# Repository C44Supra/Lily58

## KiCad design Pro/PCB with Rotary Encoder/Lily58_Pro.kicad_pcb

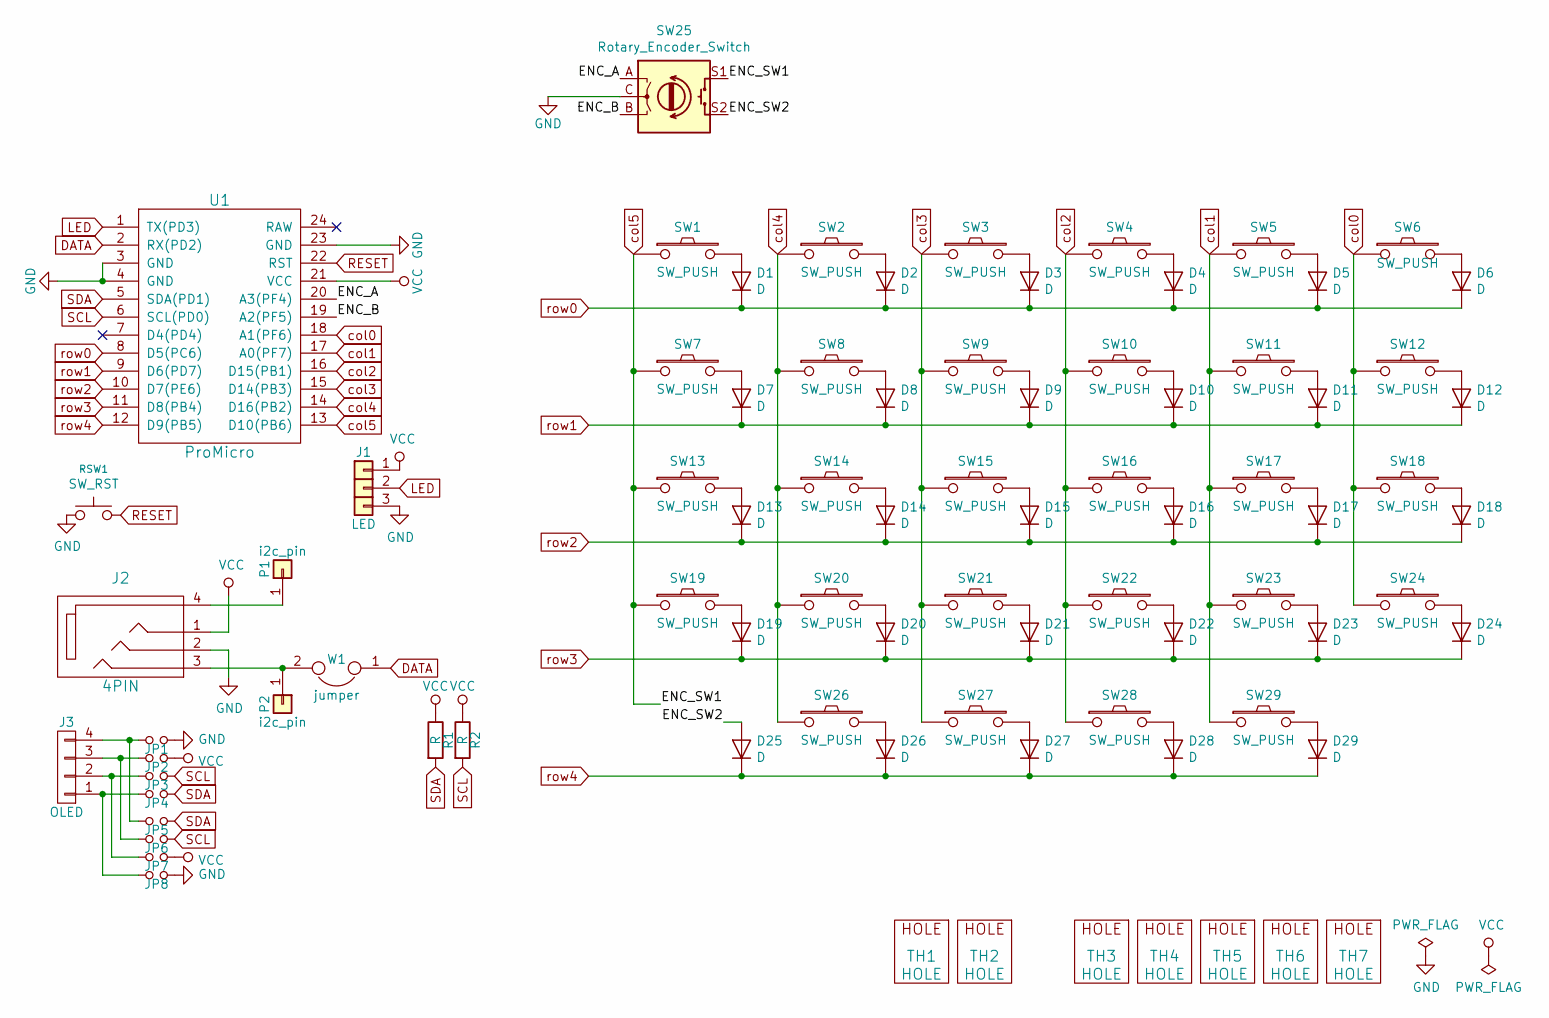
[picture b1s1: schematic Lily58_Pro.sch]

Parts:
D1, D2, D3, D4, D5, D6, D7, D8, D9, D10, D11, D12, D13, D14, D15, D16, D17, D18, D19, D20, D21, D22, D23, D24, D25, D26, D27, D28, D29: D; Diode_SOD123
J1: LED
J2: 4PIN; MJ-4PP-9
J3: OLED; OLED_4Pin
JP1, JP2, JP3, JP4, JP5, JP6, JP7, JP8: Jumper_NO_Small; Jumper
P1, P2: i2c_pin; 1pin_conn
R1, R2: R; RESISTOR_mini
RSW1: SW_RST; TACT_SWITCH_TVBP06
SW1, SW2, SW3, SW4, SW5, SW6, SW7, SW8, SW9, SW10, SW11, SW12, SW13, SW14, SW15, SW16, SW17, SW18, SW19, SW20, SW21, SW22, SW23, SW24, SW26, SW27, SW28, SW29: SW_PUSH; CherryMX_KailhLowProfile_Hotswap
SW25: Rotary_Encoder_Switch; RotaryEncoder_Alps_EC11E-Switch_Vertical_H20mm-keebio_modif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
TH1, TH2: HOLE; M2_HOLE_PCB
TH3, TH4, TH5, TH6, TH7: HOLE; HOLE_M2_TH
U1: ProMicro; ProMicro_rev2
W1: jumper; jumper_data

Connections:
/ENC_A: SW25.A, U1.20 (A3(PF4))
/ENC_B: SW25.B, U1.19 (A2(PF5))
/ENC_SW2: D25.2 (A), SW25.S2
DATA: U1.2 (RX(PD2)), W1.1
GND: J1.3, J2.2, JP1.2, JP8.2, RSW1.1, SW25.C, U1.3 (GND), U1.4 (GND), U1.23 (GND)
LED: J1.2, U1.1 (TX(PD3))
unnamed: D1.2 (A), SW1.2
unnamed: D2.2 (A), SW2.2
unnamed: D3.2 (A), SW3.2
unnamed: D4.2 (A), SW4.2
unnamed: D5.2 (A), SW5.2
unnamed: D6.2 (A), SW6.2
unnamed: D7.2 (A), SW7.2
unnamed: D8.2 (A), SW8.2
unnamed: D9.2 (A), SW9.2
unnamed: D10.2 (A), SW10.2
unnamed: D11.2 (A), SW11.2
unnamed: D12.2 (A), SW12.2
unnamed: D13.2 (A), SW13.2
unnamed: D14.2 (A), SW14.2
unnamed: D15.2 (A), SW15.2
unnamed: D16.2 (A), SW16.2
unnamed: D17.2 (A), SW17.2
unnamed: D18.2 (A), SW18.2
unnamed: D19.2 (A), SW19.2
unnamed: D20.2 (A), SW20.2
unnamed: D21.2 (A), SW21.2
unnamed: D22.2 (A), SW22.2
unnamed: D23.2 (A), SW23.2
unnamed: D24.2 (A), SW24.2
unnamed: D26.2 (A), SW26.2
unnamed: D27.2 (A), SW27.2
unnamed: D28.2 (A), SW28.2
unnamed: D29.2 (A), SW29.2
unnamed: J2.3, P2.1, W1.2
unnamed: J2.4, P1.1
unnamed: J3.1, JP4.1, JP8.1
unnamed: J3.2, JP3.1, JP7.1
unnamed: J3.3, JP2.1, JP6.1
unnamed: J3.4, JP1.1, JP5.1
RESET: RSW1.2, U1.22 (RST)
SCL: JP3.2, JP6.2, R2.2, U1.6 (SCL(PD0))
SDA: JP4.2, JP5.2, R1.2, U1.5 (SDA(PD1))
VCC: J1.1, J2.1, JP2.2, JP7.2, R1.1, R2.1, U1.21 (VCC)
col0: SW6.1, SW12.1, SW18.1, SW24.1, U1.18 (A1(PF6))
col1: SW5.1, SW11.1, SW17.1, SW23.1, SW29.1, U1.17 (A0(PF7))
col2: SW4.1, SW10.1, SW16.1, SW22.1, SW28.1, U1.16 (D15(PB1))
col3: SW3.1, SW9.1, SW15.1, SW21.1, SW27.1, U1.15 (D14(PB3))
col4: SW2.1, SW8.1, SW14.1, SW20.1, SW26.1, U1.14 (D16(PB2))
col5: SW1.1, SW7.1, SW13.1, SW19.1, SW25.S1, U1.13 (D10(PB6))
row0: D1.1 (K), D2.1 (K), D3.1 (K), D4.1 (K), D5.1 (K), D6.1 (K), U1.8 (D5(PC6))
row1: D7.1 (K), D8.1 (K), D9.1 (K), D10.1 (K), D11.1 (K), D12.1 (K), U1.9 (D6(PD7))
row2: D13.1 (K), D14.1 (K), D15.1 (K), D16.1 (K), D17.1 (K), D18.1 (K), U1.10 (D7(PE6))
row3: D19.1 (K), D20.1 (K), D21.1 (K), D22.1 (K), D23.1 (K), D24.1 (K), U1.11 (D8(PB4))
row4: D25.1 (K), D26.1 (K), D27.1 (K), D28.1 (K), D29.1 (K), U1.12 (D9(PB5))

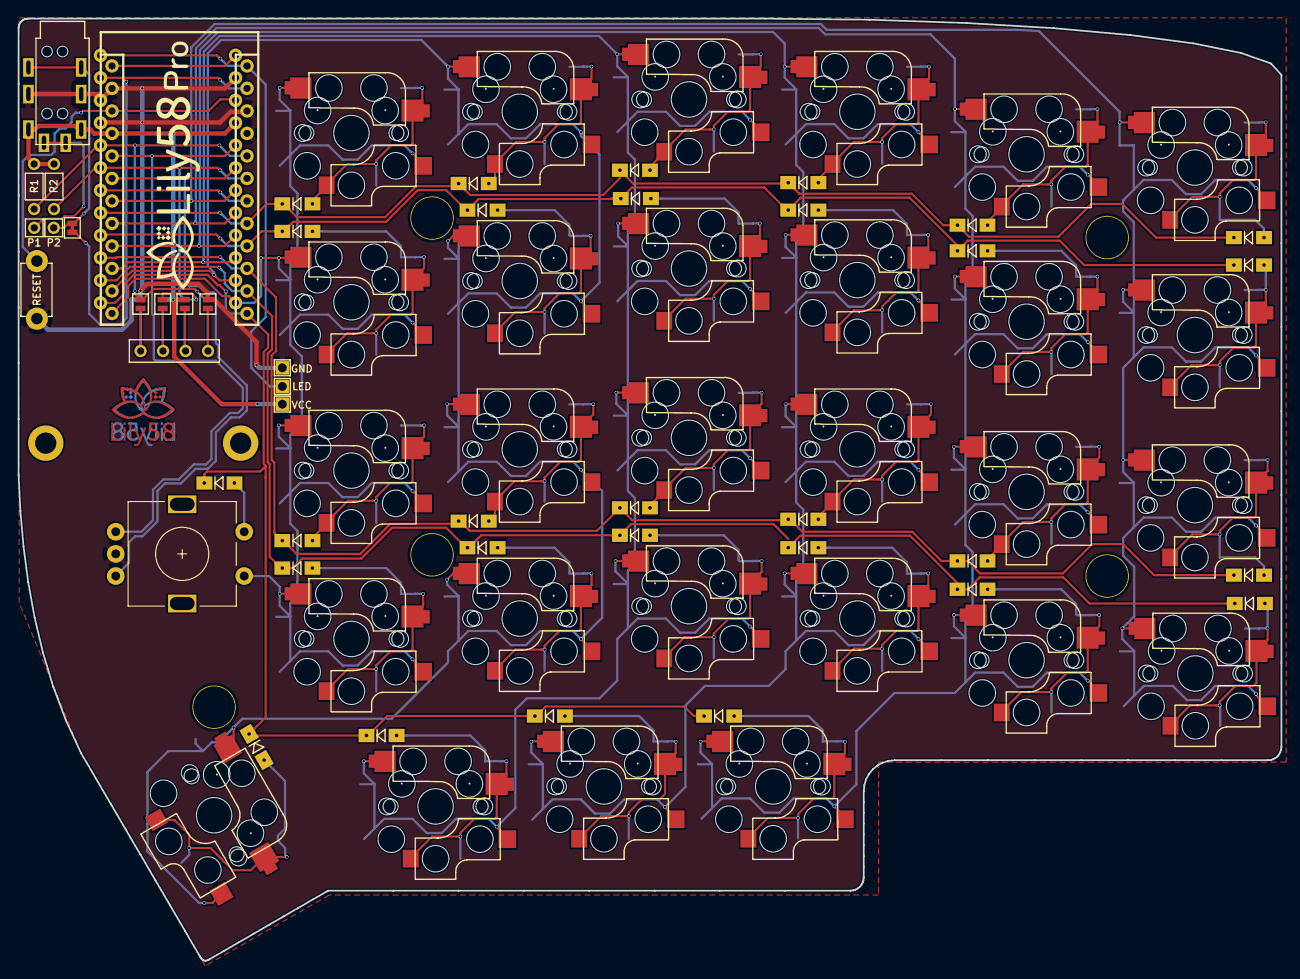
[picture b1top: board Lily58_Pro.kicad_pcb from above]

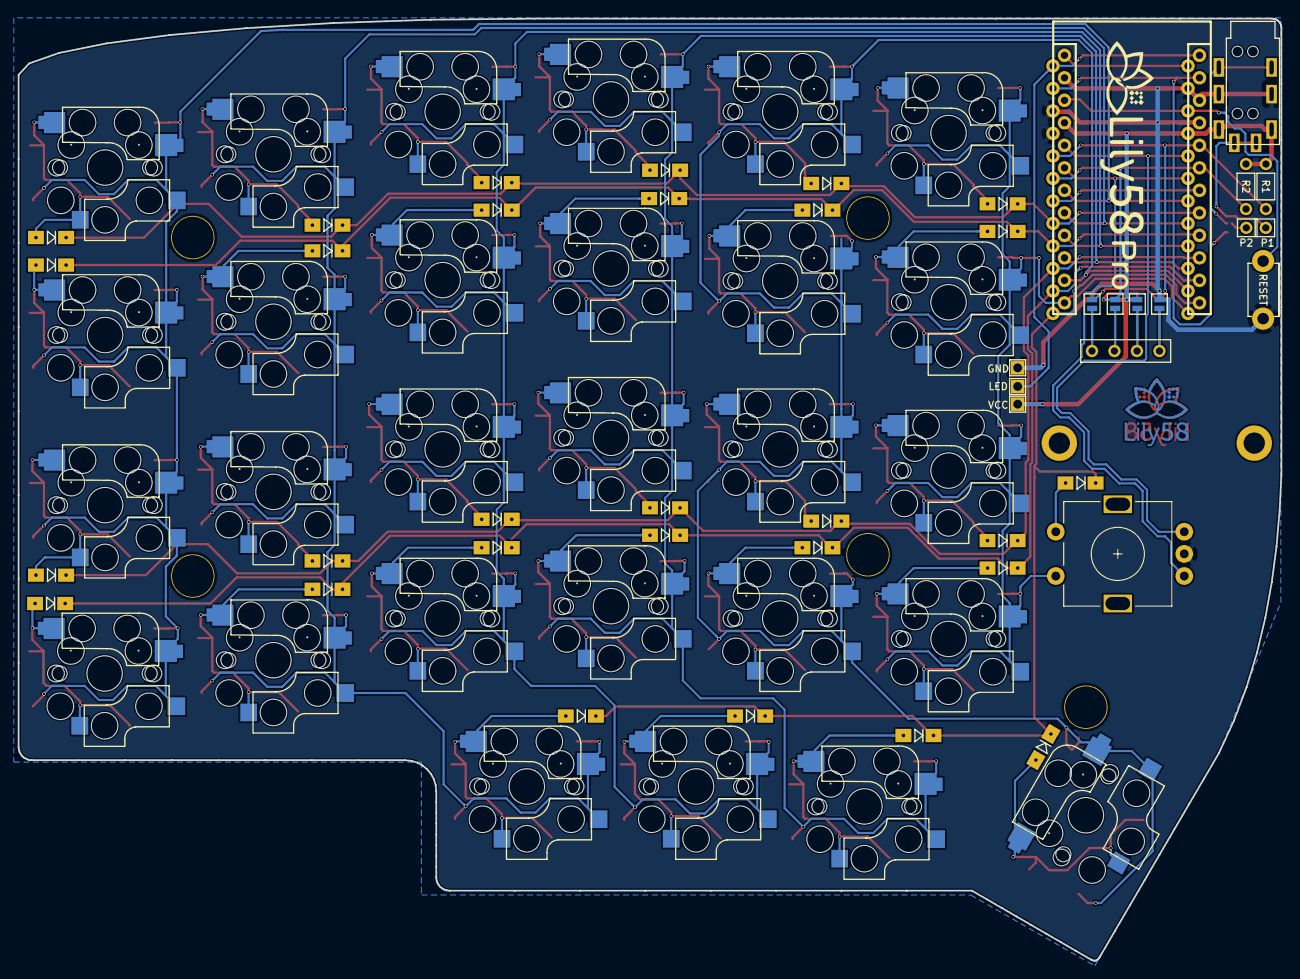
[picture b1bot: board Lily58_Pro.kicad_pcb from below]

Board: 2 copper layers, 142.5 x 106.3 mm, 83 parts (4 on the bottom side), 55 nets.

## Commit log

2019-08-20 Fixed gaps in copper fills
2019-08-20 Replaced SW25 with Rotary Encoder. Takes place of SW25 in matrix
    Removed the footprint for switch 25 and replaced it with an Alps EC11E encoder. Encoder outputs have been connected to A3(PF4) and A2(PF5). The switch part of the encoder connects to the old spot of 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
2019-08-20 removed .DS_Store files
